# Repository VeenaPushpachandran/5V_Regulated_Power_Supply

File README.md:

# 5V Regulated Power Supply – KiCad PCB Design

## Project Overview

This project involves the design and PCB layout of a 5V regulated DC power supply using the LM7805 linear voltage regulator. The circuit accepts a nominal 9V DC input and provides a regulated 5V DC output for low-power electronic applications.

The project was developed using KiCad, covering schematic capture, component selection, PCB layout, copper zone configuration, design rule checking (DRC), and manufacturing file preparation.

## Project Specifications

| Parameter | Specification |
|---|---|
| Input Voltage | 9V DC nominal |
| Output Voltage | 5V DC regulated |
| Voltage Regulator | LM7805 |
| Target Load Current | 100mA |
| PCB Design Software | KiCad |
| PCB Dimensions | Approximately 50mm × 35mm |
| PCB Layers | 2-layer design |

## Circuit Description

The circuit uses an LM7805 linear voltage regulator to convert the 9V DC input into a regulated 5V DC output.

The circuit includes:

- Input electrolytic capacitor for bulk filtering.
- Input ceramic bypass capacitor for high-frequency noise suppression.
- LM7805 linear voltage regulator for voltage regulation.
- Output ceramic bypass capacitor for stability and transient response.
- Output electrolytic capacitor for additional filtering.
- Two-pin input and output connectors.

## Component Selection

| Reference | Component | Value |
|---|---|---|
| U1 | LM7805 Voltage Regulator | 5V |
| C1 | Electrolytic Capacitor | 10µF |
| C2 | Ceramic Capacitor | 100nF |
| C3 | Ceramic Capacitor | 100nF |
| C4 | Electrolytic Capacitor | 10µF |
| J1 | Input Connector | 2-pin |
| J2 | Output Connector | 2-pin |

## PCB Design and Layout

The PCB was designed in KiCad using a two-layer layout.

Design activities included:

- Schematic capture and electrical net assignment.
- Component footprint assignment.
- PCB component placement and routing.
- Power and ground routing.
- Bottom-layer GND copper zone configuration.
- Board outline definition.
- Design Rule Check (DRC).

## Design Calculations

At a nominal 9V input and 5V output:

**Voltage drop across regulator:**

Vdrop = 9V − 5V = 4V

**Estimated regulator power dissipation at 100mA:**

P = (Vin − Vout) × I

P = (9V − 5V) × 0.1A = 0.4W

**Equivalent load resistance at 100mA:**

R = V / I = 5V / 0.1A = 50Ω

Thermal performance and component ratings must be verified before operation at the target load.

## Design Rule Check (DRC)

The KiCad Design Rule Check was completed with the following reported results:

- DRC violations: 0
- Unconnected pads: 0
- Footprint errors: 0

Some optional DRC checks were configured as ignored and require separate review.

## Project Documentation

The repository includes supporting engineering documentation:

- Project Overview
- Bill of Materials (BOM)
- Design Calculations
- Component Selection Justification
- DRC Report
- PCB design screenshots

## Manufacturing Files

Gerber and drill files are prepared for PCB fabrication. These files should be independently checked in a Gerber viewer before manufacturing.

## Project Status

**PCB design and initial DRC completed. Physical prototype testing is pending.**

The design has not yet been validated through physical measurements. Output voltage regulation, load performance, ripple, and thermal behaviour remain to be tested on a fabricated prototype.

## Software and Tools

- KiCad – Schematic capture and PCB design
- Gerber Viewer – Manufacturing output inspection
- GitHub – Project version control and documentation

## Skills Demonstrated

- Electronic circuit design
- Linear voltage regulation
- Electronic component selection
- Schematic capture
- PCB layout and routing
- Through-hole component footprints
- Ground copper zone configuration
- Design Rule Checking
- Gerber and drill file generation
- Engineering documentation

---

**Author:** Veena Pushpachandran, Engineer-in-Training (EIT) – Engineers Nova Scotia

**Project:** 5V Regulated Power Supply PCB Design

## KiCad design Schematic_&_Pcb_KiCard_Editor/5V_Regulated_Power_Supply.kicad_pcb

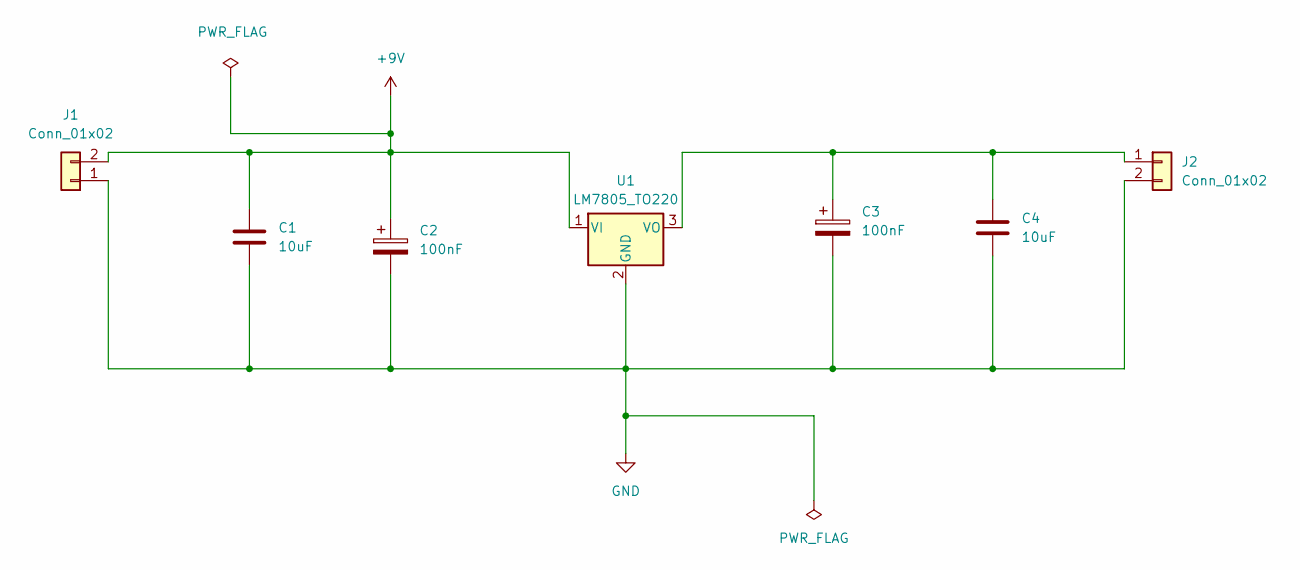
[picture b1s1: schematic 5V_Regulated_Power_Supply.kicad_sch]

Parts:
C1, C4: 10uF; C_Disc_D5.0mm_W2.5mm_P2.50mm
C2, C3: 100nF; CP_Radial_D5.0mm_P2.50mm
J1, J2: Conn_01x02; TerminalBlock_Phoenix_MKDS-1,5-2-5.08_1x02_P5.08mm_Horizont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
U1: LM7805_TO220; TO-220-3_Vertical

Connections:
+9V: C1.1, C2.1, J1.2, U1.1 (VI)
GND: C1.2, C2.2, C3.2, C4.2, J1.1, J2.2, U1.2 (GND)
unnamed: C3.1, C4.1, J2.1, U1.3 (VO)

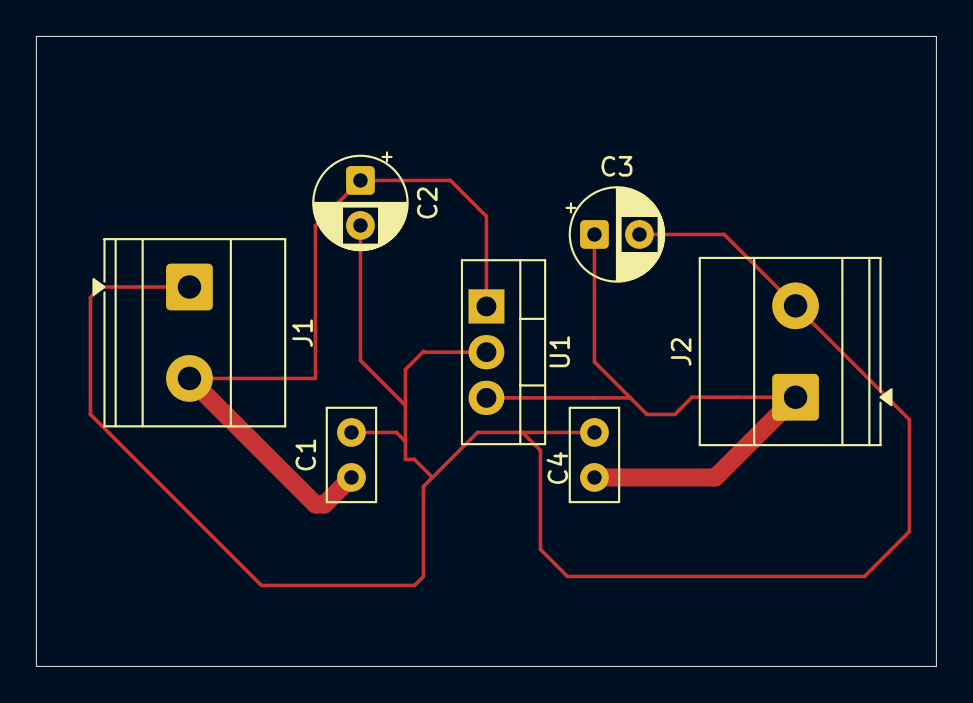
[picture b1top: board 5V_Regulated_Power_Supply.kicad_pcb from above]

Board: 2 copper layers, 50.0 x 35.0 mm, 7 parts (0 on the bottom side), 3 nets.

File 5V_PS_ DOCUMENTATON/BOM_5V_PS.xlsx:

Reference | Component Description | Value / Part Number | Quantity | Electrical Rating | Package | KiCad Footprint | Function | Selection Justification
U1 | Voltage regulator | LM7805 | 1 | Fixed 5V output | TO-220-3 | Package_TO_SOT_THT:TO-220-3_Vertical | Voltage regulation | Selected to provide a regulated 5V DC output using a linear regulation method.
C1 | Electrolytic capacitor | 10 µF | 1 | 25V | Radial THT | Capacitor_THT:C_Disc_D5.0mm_W2.5mm_P2.50mm | Input bulk filtering | Provides input bulk capacitance to help reduce supply variations.
C2 | Ceramic capacitor | 100 nF | 1 | Verify selected rating | Radial/Disc THT | Capacitor_THT:CP_Radial_D5.0mm_P2.50mm | Input bypassing | Provides high-frequency input bypassing near the regulator.
C3 | Ceramic capacitor | 100 nF | 1 | Verify selected rating | Radial/Disc THT | Capacitor_THT:CP_Radial_D5.0mm_P2.50mm | Output bypassing | Provides high-frequency output bypassing.
C4 | Electrolytic capacitor | 10 µF | 1 | 10V minimum; verify actual selection | Radial THT | Capacitor_THT:C_Disc_D5.0mm_W2.5mm_P2.50mm | Output bulk filtering | Helps support output filtering and transient response.
J1 | 2-pin input connector | 2-pin | 1 | Suitable for input voltage/current | THT terminal block | TerminalBlock_Phoenix:TerminalBlock_Phoenix_MKDS-1,5-2-5.08_1x02_P5.08mm_Horizo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 | DC input | Provides a removable two-wire DC input connection.
J2 | 2-pin output connector | 2-pin | 1 | Suitable for output voltage/current | THT terminal block | TerminalBlock_Phoenix:TerminalBlock_Phoenix_MKDS-1,5-2-5.08_1x02_P5.08mm_Horizo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 | Regulated DC output | Provides a removable two-wire regulated output connection.
